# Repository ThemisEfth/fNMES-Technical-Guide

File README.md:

# fNMES-GUI: Computer-controlled Electrical Stimulation of Facial Muscles

This repository contains the Python script for a graphical user interface (GUI) designed to control electrical stimulators via Arduino boards, facilitating precise adjustment of electrical stimulation parameters. This repository accompanies the paper titled: *Computer-controlled electrical stimulation of facial muscles by facial neuromuscular electrical stimulation (fNMES): Hardware and software solutions*.

## Contents

- [Requirements](#requirements)
- [GUI Functionality](#gui-functionality)
  - [Command Codes](#command-codes)
  - [GUI Commands](#gui-commands)
  - [Button Actions](#button-actions)
  - [Configuration Commands](#configuration-commands)
  - [Additional Details](#additional-details)
- [Getting Started with fNMES-GUI for Beginners](#getting-started-with-fnmes-gui-for-beginners)
  - [Prerequisites](#prerequisites)
  - [Download the Script](#download-the-script)
  - [Running the Script](#running-the-script)
  - [Configure the Port](#configure-the-port)
  - [Running the GUI](#running-the-gui)
- [Arduino .ino Code](#arduino-ino-code)
- [License](#license)

## Video guide

## Requirements

The GUI is developed using Python 3.8.5 and utilizes the `tkinter` package for the interface. Additional Python modules required are:
- `serial`: for sending serial commands to Arduino
- `time`: to incorporate delays in commands using `time.sleep`

Ensure the Arduino is set with a BaudRate of 19200. Connection ports differ based on the operating system:
- **Windows**: Use a ‘COM’ port.
- **Mac OS & Linux**: Use a “/dev/ttyACM0” location.

### Finding Your Port

#### Mac OS & Linux

1. Open terminal
2. Type: `ls /dev/tty*` and note the port number listed for `/dev/ttyUSB*` or `/dev/ttyACM*`
3. The port number is represented with `*` here.

#### Windows

1. Open Device Manager (Start → Control Panel → Hardware and Sound → Device Manager)
2. Look under “Ports” to find the matching COM port.
3. Note the number in the bracket behind the port description.

## GUI Functionality

The GUI interfaces with the Arduino by sending Hex commands to trigger specific actions in the firmware (DS5 controlled, built by Andreas Gartus, 2020).

### Command Codes

- **Matlab**: Use decimal codes (e.g., `99` for start)
- **Python**: Use Hex codes without the leading `0` (e.g., `xFF` for start)

### GUI Commands

#### Button Actions

- **Start**: `255 (0xFF)`: Initiates device, sets default settings, and opens the port for commands.
- **Blink**: `99 (0x63)`: Blinks the display as a command test (do not use continuously).
- **Display Off**: `69 (0x45) + 1`: Turns the display off.
- **Display On**: `68 (0x44) + 0`: Turns the display on.
- **Reset Pulse**: `78 (0x4E)`: Resets pulse count to zero.
- **Query Data**: `65 (0x41)`: Displays current settings on Arduino.
- **Set All**: Sends all input parameters to the Arduino.
- **START**: `80 (0x50)`: Begins pulse sequence.
- **STOP**: `33 (0x21)`: Emergency stop for pulse sequence.
- **Close Port**: Closes the serial port. Restart the GUI and Arduino connection if needed.

#### Configuration Commands

- **Bipolar OpAmp Enabled**: `98 (0x62)`: Set pulse mode to bipolar.
- **Monopolar OpAmp Enabled**: `97 (0x61)`: Set pulse mode to monopolar with OpAmp.
- **Monopolar OpAmp Disabled**: `96 (0x60)`: Set pulse mode to monopolar without OpAmp.

### Additional Details

- OpAmp adjustments are necessary for enabling bipolar stimulation.
- Monopolar stimulation can be achieved with either setting of the OpAmp.

## Getting Started with fNMES-GUI for Beginners

To use the fNMES-GUI, you'll need a basic setup and understanding of how to run Python scripts. Here's a step-by-step guide to get you started:

### Prerequisites

Before running the GUI, make sure you have the following:
- **Python Installed**: Install Python 3.8.5 or higher. You can download it from [python.org](https://www.python.org/downloads/).
- **Python Modules**: Ensure the `tkinter`, `serial`, and `time` modules are installed. You can install any required modules using pip. For example:
  ```bash
  pip install pyserial
  ```

### Download the Script

- **From GitHub**: Navigate to the GitHub repository where the fNMES-GUI script is hosted.
  - Click on the `Code` button and select `Download ZIP`, or clone the repository using:
    ```bash
    git clone git@github.com:ThemisEfth/fNMES-Technical-Guide.git](https://github.com/ThemisEfth/fNMES-Technical-Guide)
    ```
  - Extract the ZIP file if you downloaded it.

## GUI Types

There are two types of GUIs available: a condensed version and a full version.

### Condensed GUI

The condensed GUI focuses on simplifying the user interface by reducing the number of input fields and emphasizing the use of milliseconds over microseconds for input parameters. This version is recommended for most users due to its simplicity and ease of use.

### Full GUI

The full GUI provides a more comprehensive interface with additional input fields, allowing for more detailed control over the stimulation parameters. This version includes inputs for both milliseconds and microseconds, giving users more flexibility in their settings.

### Choosing the Right GUI

- **Condensed GUI**: Use this version if you prefer a simpler interface with fewer input fields and a focus on using milliseconds for timing parameters.
- **Full GUI**: Choose this version if you need more detailed control over the stimulation parameters and require inputs for both milliseconds and microseconds.

To switch between the GUIs, simply use the corresponding Python script provided in the repository for each version.

### Running the Script

Once you have Python and the script on your local machine, you can run the script using one of the following methods:

#### Using an Integrated Development Environment (IDE)

- Open your preferred IDE (e.g., PyCharm, VSCode).
- Load the script into the IDE.

### Configure the Port

Before running the GUI, you need to configure the script to communicate with the correct Arduino port:
- **Find the Port**:
  - Use the instructions provided in the "Finding Your Port" section above to identify your COM port (Windows) or device path (Mac/Linux).
- **Edit the Script**:
  - Open the Python script in a text editor or IDE.
  - Locate the line of code where the port is specified, which might look something like this:
    ```python
    arduino = serial.Serial('COM3', 19200)
    ```
  - Replace `'COM3'` with the port you identified earlier.
  - Save the changes.

### Running the GUI

After configuring the port, run the script in the IDE.

Alternatively, you can run the Python file in the terminal/command line:

#### Using the Command Line

- Open Command Prompt (Windows) or Terminal (Mac and Linux).
- Navigate to the directory containing the script. For example:
  ```bash
  cd path/to/your/script
  ```
- Run the script by typing:
  ```bash
  python fNMES_GUI.py
  ```

The GUI should launch, allowing you to interact with the Arduino-connected stimulator.

## Arduino .ino Code

The repository also includes the Arduino .ino file, which is essential for the operation of the fNMES system. This firmware enables the Arduino to:

- Receive commands from the Python GUI via serial communication.
- Generate pulse trains with adjustable parameters such as pulse width, repetition rate, and repetition period.
- Support both bipolar and monopolar stimulation modes.
- Integrate an external operational amplifier (OpAmp) for enhanced precision and control over the output voltage.

The Arduino firmware is designed to be flexible, allowing researchers to tailor the electrical stimulation parameters to their specific experimental needs. It facilitates the delivery of precise electrical pulses to facial muscles, making it a valuable tool for studying facial feedback effects and their neurological basis.

### Loading the .ino Firmware onto Your Arduino

To load the .ino firmware onto your Arduino, follow these steps:

1. **Install the Arduino IDE**:
   - Download and install the Arduino IDE from the Arduino website.
2. **Connect Your Arduino**:
   - Connect your Arduino board to your computer using a USB cable.
3. **Open the .ino File**:
   - Launch the Arduino IDE.
   - Go to File > Open and navigate to the .ino file included in this repository. Open the file.
4. **Select Your Board and Port**:
   - Go to Tools > Board and select the appropriate Arduino board (e.g., Arduino Uno).
   - Go to Tools > Port and select the port that your Arduino is connected to (e.g., COM3 on Windows, /dev/cu.usbmodem146301 on macOS).
5. **Upload the Firmware**:
   - Click the Upload button (right arrow icon) in the Arduino IDE toolbar. This will compile the code and upload it to your Arduino board.
   - Ensure the upload is successful by looking for the “Done uploading” message in the IDE.

Once the firmware is successfully uploaded, your Arduino is ready to communicate with the Python GUI and execute the electrical stimulation commands.

## DAC Controller Subfolder

The `dac_controller` subfolder contains the necessary files for building and configuring the DAC (Digital-to-Analog Converter) controller. This includes both the Arduino code and the schematics for assembling the DAC.

### Contents of the `dac_controller` Subfolder

- `TMR0521_Library.kicad_sym`: KiCad symbol library file.
- `dac_controller.kicad_pcb`: KiCad PCB design file.
- `dac_controller.kicad_prl`: KiCad project file.
- `dac_controller.kicad_pro`: KiCad project file.
- `dac_controller.kicad_sch`: KiCad schematic file.
- `dac_controller.net`: KiCad netlist file.
- `dac_controller_pcb_1.1.pdf`: PDF file of the PCB layout.
- `dac_controller_schematic_1.1.pdf`: PDF file of the schematic diagram.
- `sym-lib-table`: Symbol library table file.

These files provide all the necessary information to build the DAC controller, which is used to control the analogue output signals for the fNMES system. Below are the details on how to use the provided files to assemble and configure the DAC controller.

### Using the DAC Controller Files

1. **KiCad Design Files**:
   - **KiCad Project Files**: Open the `dac_controller.kicad_pro` project file in KiCad to access the full design of the DAC controller.
   - **Schematic File**: The `dac_controller.kicad_sch` file contains the schematic diagram, which shows the circuit design.
   - **PCB Design File**: The `dac_controller.kicad_pcb` file includes the layout of the PCB, which is used to manufacture the physical circuit board.
2. **PDF Documentation**:
   - **Schematic Diagram**: The `dac_controller_schematic_1.1.pdf` file provides a PDF version of the schematic diagram for easy reference.
   - **PCB Layout**: The `dac_controller_pcb_1.1.pdf` file offers a PDF version of the PCB layout, which can be used to understand the physical placement of components on the board.
3. **Component Library**:
   - **Symbol Library**: The `TMR0521_Library.kicad_sym` file contains the symbols for components used in the DAC controller design.
4. **Netlist**:
   - **Netlist File**: The `dac_controller.net` file provides the netlist for the DAC controller, which is used to link the schematic components with the PCB layout.
5. **Library Table**:
   - **Symbol Library Table**: The `sym-lib-table` file helps KiCad locate the component symbols needed for the design.

### Building the DAC Controller

Follow these steps to build the DAC controller:

1. **Open the KiCad Project**:
   - Download and install KiCad from the KiCad website.
   - Open KiCad and load the `dac_controller.kicad_pro` project file.
2. **Review the Schematic**:
   - Open the `dac_controller.kicad_sch` file in KiCad’s Eeschema tool to review the schematic diagram.
   - Ensure all components and connections match the design specifications.
3. **Prepare the PCB Layout**:
   - Open the `dac_controller.kicad_pcb` file in KiCad’s PCBnew tool to review the PCB layout.
   - Make any necessary adjustments to the layout before manufacturing.
4. **Generate Gerber Files**:
   - Generate Gerber files from the PCB layout, which will be used by PCB manufacturers to create the physical board.
5. **Assemble the PCB**:
   - Once the PCB is manufactured, assemble the components as per the schematic and PCB layout. Refer to the `dac_controller_schematic_1.1.pdf` and `dac_controller_pcb_1.1.pdf` files for guidance.
6. **Upload the Firmware**: Use the provided Arduino .ino file to program the Arduino microcontroller that interfaces with the DAC controller.

### Key Parameters of fNMES

- **Pulse Phase**: Monophasic (unidirectional) and biphasic (bidirectional) waveforms.
- **Waveform Shape**: Typically, a square wave is used for its effectiveness and comfort.
- **Pulse Width**: The duration of the ion flow is critical for stimulating facial nerves effectively.
- **Frequency**: Measured in Hz, affects muscle contraction quality and fatigue rate.
- **Stimulation Intensity**: Delivered in milliamperes (mA), influences muscle contraction strength.

The provided Arduino code and hardware schematics enable the integration of these parameters into the fNMES setup, allowing for precise and reproducible facial muscle stimulation in experimental settings.

## License

This project is licensed under the MIT License - see the [LICENSE.md](LICENSE.md) file for details. This license allows you to use, modify, and distribute the software as you see fit.

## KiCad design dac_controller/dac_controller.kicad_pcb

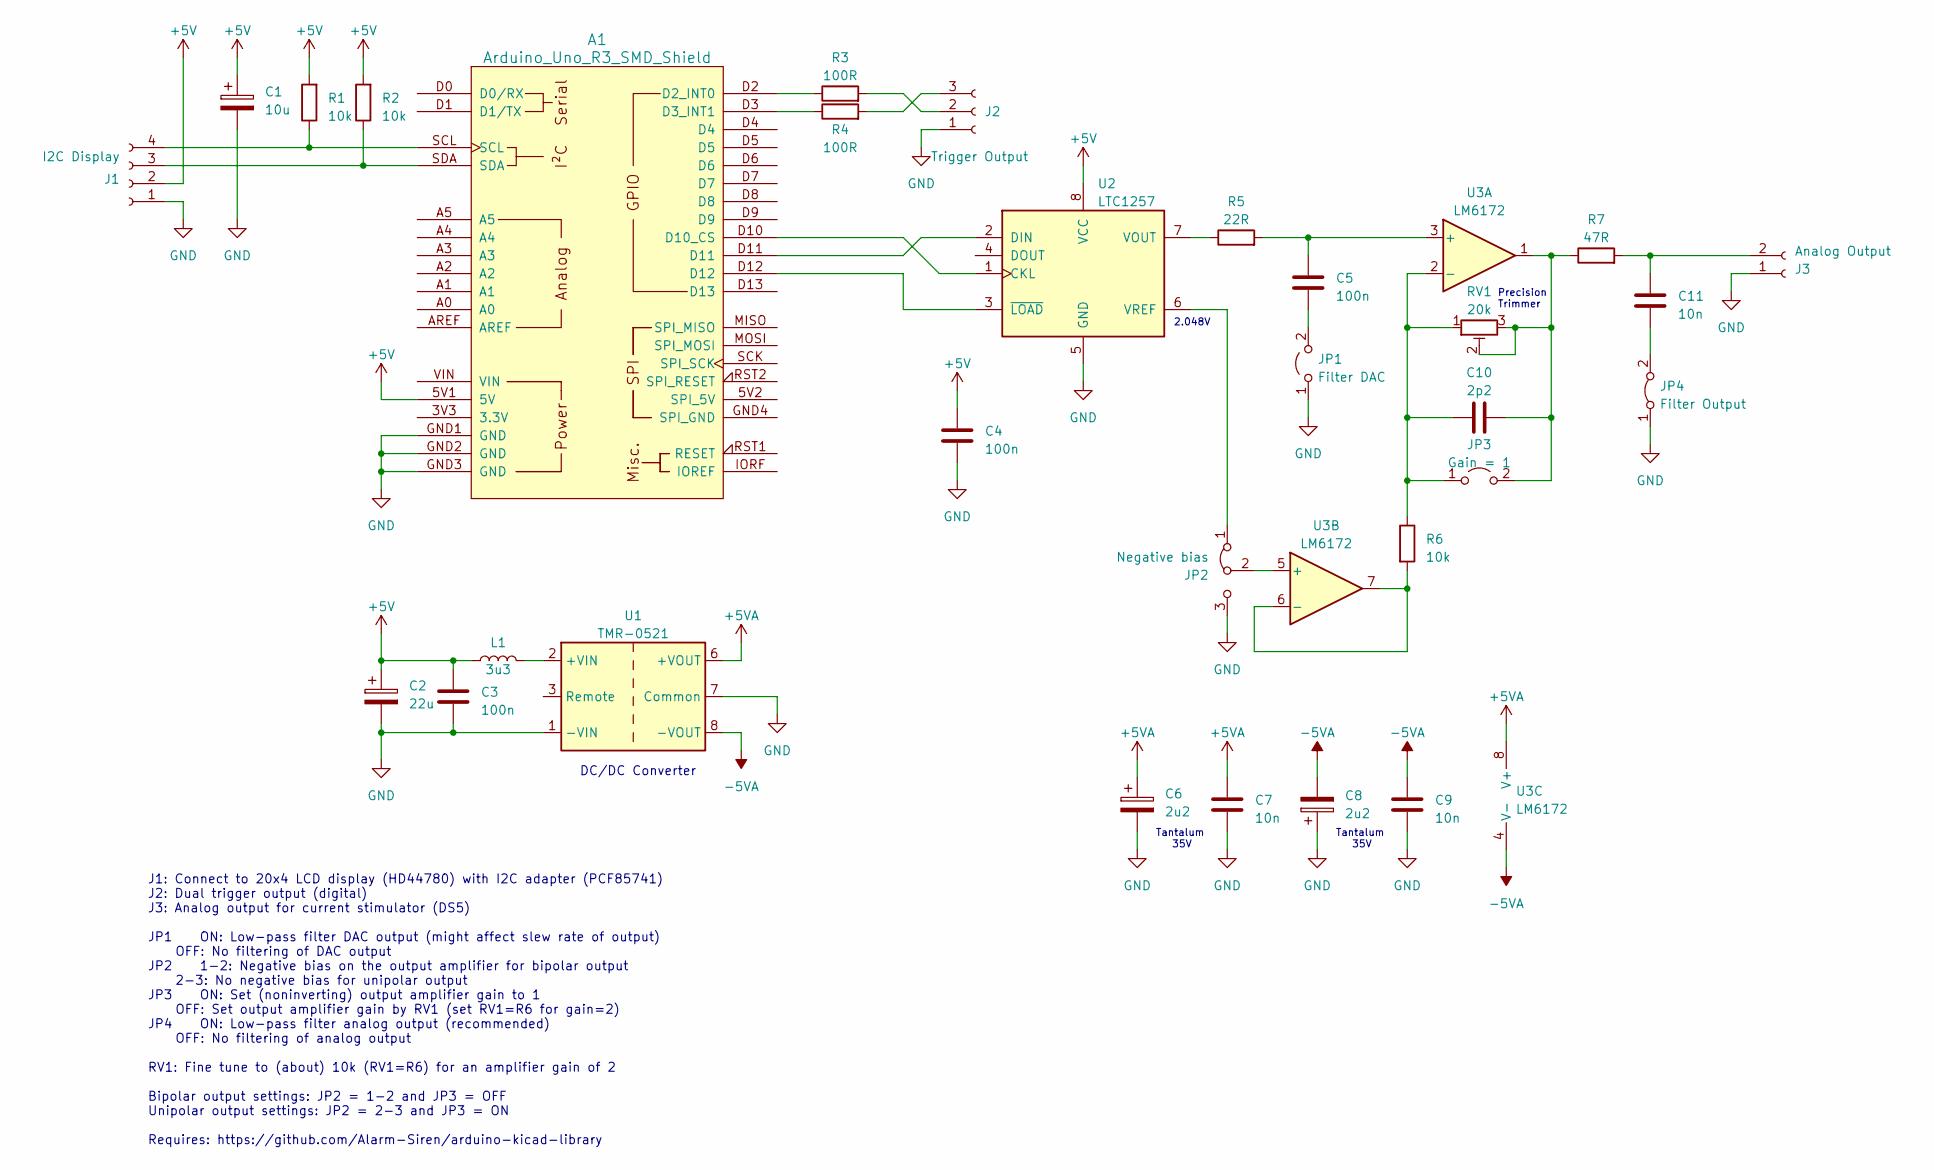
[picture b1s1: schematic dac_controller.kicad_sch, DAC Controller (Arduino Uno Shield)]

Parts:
A1: Arduino_Uno_R3_SMD_Shield; Arduino_Uno_R3_Shield
C1: 10u; CP_Radial_D5.0mm_P2.50mm
C2: 22u; CP_Radial_D5.0mm_P2.50mm
C3, C4: 100n; C_Disc_D3.0mm_W1.6mm_P2.50mm
C5: 100n; C_Disc_D4.3mm_W1.9mm_P5.00mm
C6, C8: 2u2; CP_Radial_Tantal_D4.5mm_P2.50mm
C7, C9, C11: 10n; C_Disc_D3.0mm_W1.6mm_P2.50mm
C10: 2p2; C_Disc_D4.3mm_W1.9mm_P5.00mm
J1: I2C Display; Molex_KK-254_AE-6410-04A_1x04_P2.54mm_Vertical
J2: Trigger Output; Molex_KK-254_AE-6410-03A_1x03_P2.54mm_Vertical
J3: Analog Output; Molex_KK-254_AE-6410-02A_1x02_P2.54mm_Vertical
JP1: Filter DAC; PinHeader_1x02_P2.54mm_Vertical
JP2: Negative bias; PinHeader_1x03_P2.54mm_Vertical
JP3: Gain = 1; PinHeader_1x02_P2.54mm_Vertical
JP4: Filter Output; PinHeader_1x02_P2.54mm_Vertical
L1: 3u3; L_Axial_L5.3mm_D2.2mm_P10.16mm_Horizontal_Vishay_IM-1
R1: 10k; R_Axial_DIN0207_L6.3mm_D2.5mm_P5.08mm_Vertical
R2: 10k; R_Axial_DIN0207_L6.3mm_D2.5mm_P2.54mm_Vertical
R3, R4: 100R; R_Axial_DIN0207_L6.3mm_D2.5mm_P10.16mm_Horizontal
R5: 22R; R_Axial_DIN0207_L6.3mm_D2.5mm_P7.62mm_Horizontal
R6: 10k; R_Axial_DIN0204_L3.6mm_D1.6mm_P2.54mm_Vertical
R7: 47R; R_Axial_DIN0207_L6.3mm_D2.5mm_P7.62mm_Horizontal
RV1: 20k; Potentiometer_Bourns_3005_Horizontal
U1: TMR-0521; Converter_DCDC_TRACO_TMR-xxxx_THT
U2: LTC1257; DIP-8_W7.62mm
U3: LM6172; DIP-8_W7.62mm

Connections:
+5V: A1.5V1 (5V), C1.1, C2.1, C3.1, C4.1, J1.2, L1.1, R1.2, R2.2, U2.8 (VCC)
+5VA: C6.1, C7.1, U1.6 (+VOUT), U3.8 (V+)
-5VA: C8.2, C9.1, U1.8 (-VOUT), U3.4 (V-)
GND: A1.GND1 (GND), A1.GND2 (GND), A1.GND3 (GND), C1.2, C2.2, C3.2, C4.2, C6.2, C7.2, C8.1, C9.2, J1.1, J2.1, J3.1, JP1.1 (A), JP2.3 (B), JP4.1 (A), U1.1 (-VIN), U1.7 (Common), U2.5 (GND)
unnamed: A1.D2 (D2_INT0), R3.1
unnamed: A1.D3 (D3_INT1), R4.1
unnamed: A1.D10 (D10_CS), U2.1 (CKL)
unnamed: A1.SDA, J1.3, R2.1
unnamed: A1.SCL, J1.4, R1.1
unnamed: J2.2, R3.2
unnamed: J2.3, R4.2
unnamed: C11.1, J3.2, R7.2
unnamed: C5.2, JP1.2 (B)
unnamed: JP2.1 (A), U2.6 (VREF)
unnamed: JP2.2 (C), U3.5 (+)
unnamed: C10.1, JP3.1 (A), R6.1, RV1.1, U3.2 (-)
unnamed: C10.2, JP3.2 (B), R7.1, RV1.2, RV1.3, U3.1
unnamed: C11.2, JP4.2 (B)
unnamed: L1.2, U1.2 (+VIN)
unnamed: A1.D11, U2.2 (DIN)
unnamed: R5.1, U2.7 (VOUT)
unnamed: A1.D12, U2.3 (~LOAD)
unnamed: C5.1, R5.2, U3.3 (+)
unnamed: R6.2, U3.6 (-), U3.7

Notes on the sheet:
J1: Connect to 20x4 LCD display (HD44780) with I2C adapter (PCF85741) J2: Dual trigger output (digital) J3: Analog output for current stimulator (DS5) JP1 ON: Low-pass filter DAC output (might affect slew rate of output) OFF: No filtering of DAC output JP2 1-2: Negative bias on the output amplifier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
2.048V
DC/DC Converter
Tantalum 35V
Precision Trimmer

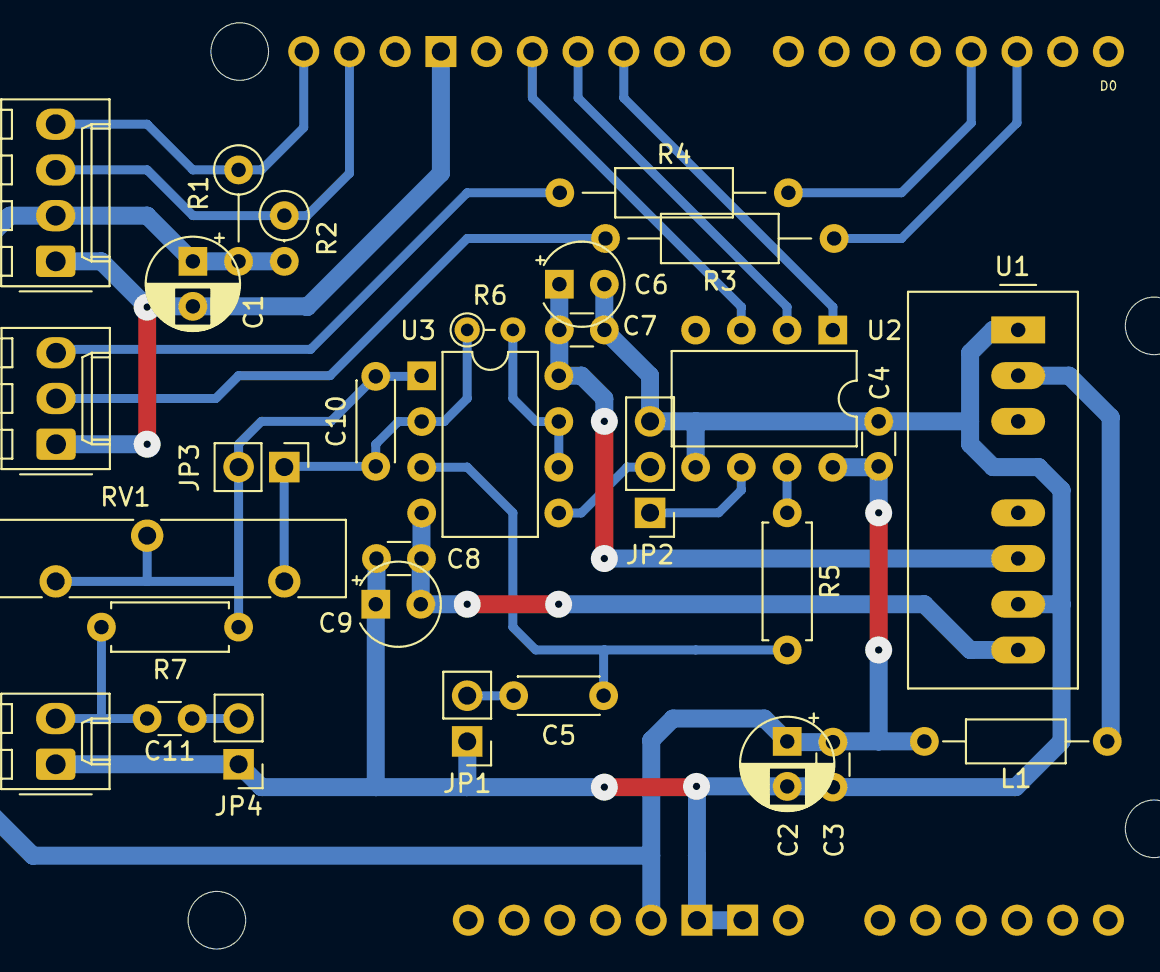
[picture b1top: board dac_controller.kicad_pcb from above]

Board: 2 copper layers, 31 parts (0 on the bottom side), 24 nets.

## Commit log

2024-08-07 Add images
2024-08-07 add new images
2024-08-13 Update README.md
    Add link to video walkthrough
2024-08-13 Update README.md
    fix typo
2024-08-14 Update README.md
    fix youtube link
2024-08-14 Update README.md
    fix youtube link v2

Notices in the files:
dac_controller/dac_controller.kicad_pcb:
License: CC-BY-SA-4.0
